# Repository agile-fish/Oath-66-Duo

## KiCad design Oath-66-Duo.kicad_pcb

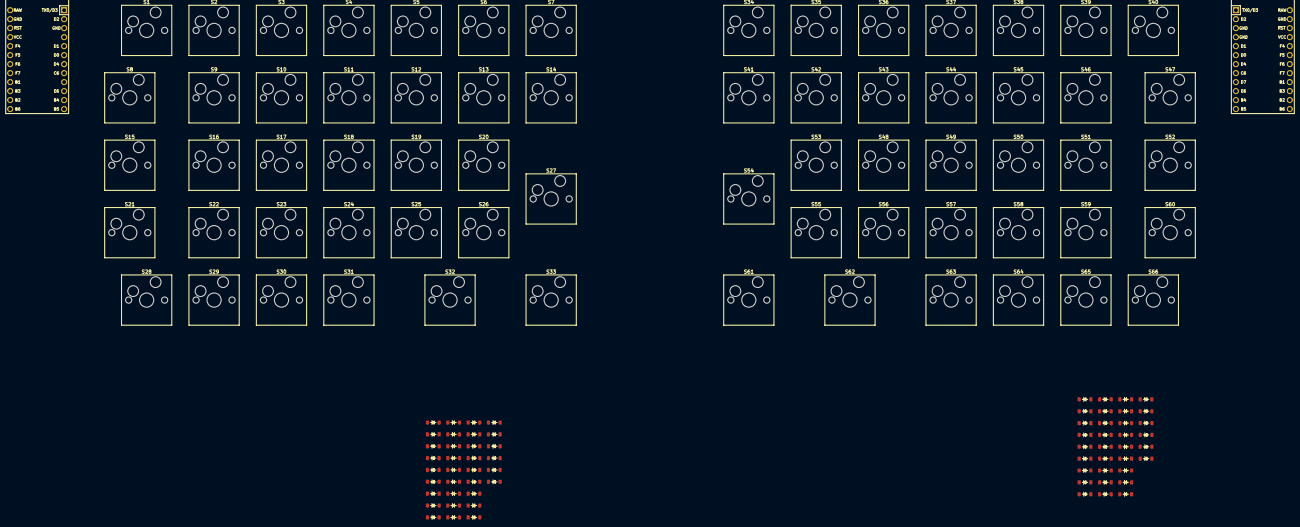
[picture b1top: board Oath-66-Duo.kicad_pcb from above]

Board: 2 copper layers, 134 parts (1 on the bottom side), 89 nets, no tracks yet.

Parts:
D1, D2, D3, D4, D5, D6, D7, D8, D9, D10, D11, D12, D13, D14, D15, D16, D17, D18, D19, D20, D21, D22, D23, D24, D25, D26, D27, D28, D29, D30, D31, D32, D33, D34, D35, D36, D37, D38, D39, D40, D41, D42, D43, D44, D45, D46, D47, D48, D49, D50, D51, D52, D53, D54, D55, D56, D57, D58, D59, D60, D61, D62, D63, D64, D65, D66: Diode; Diode_SOD-123
S1, S2, S3, S4, S5, S6, S7, S9, S10, S11, S12, S13, S14, S16, S17, S18, S19, S20, S22, S23, S24, S25, S26, S28, S29, S30, S31, S33, S34, S35, S36, S37, S38, S39, S40, S41, S42, S43, S44, S45, S46, S48, S49, S50, S51, S53, S55, S56, S57, S58, S59, S61, S63, S64, S65, S66: Keyswitch; Hotswap_MX_1.00u
S8, S15, S21, S47, S52, S60: Keyswitch; Hotswap_MX_1.50u
S27, S54: Keyswitch; Hotswap_MX_2.00u_90deg
S32, S62: Keyswitch; Hotswap_MX_2.00u
U1, U2: Arduino_Pro_Micro

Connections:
/Oath-66-Duo-Left/Col 0: S1.1, S8.1, S15.1, S21.1, S28.1, U1.8 (5/PC6)
/Oath-66-Duo-Left/Col 1: S2.1, S9.1, S16.1, S22.1, S29.1, U1.10 (7/PE6)
/Oath-66-Duo-Left/Col 2: S3.1, S10.1, S17.1, S23.1, S30.1, U1.11 (8/PB4)
/Oath-66-Duo-Left/Col 3: S4.1, S11.1, S18.1, S24.1, S31.1, U1.15 (14/PB3)
/Oath-66-Duo-Left/Col 4: S5.1, S12.1, S19.1, S25.1, S32.1, U1.13 (10/PB6)
/Oath-66-Duo-Left/Col 5: S6.1, S13.1, S20.1, S26.1, U1.5 (2/PD1)
/Oath-66-Duo-Left/Col 6: S7.1, S14.1, S27.1, S33.1, U1.6 (3/PD0)
/Oath-66-Duo-Left/Row 0: D1.1 (K), D2.1 (K), D3.1 (K), D4.1 (K), D5.1 (K), D6.1 (K), D7.1 (K), U1.7 (4/PD4)
/Oath-66-Duo-Left/Row 1: D8.1 (K), D9.1 (K), D10.1 (K), D11.1 (K), D12.1 (K), D13.1 (K), D14.1 (K), U1.9 (6/PD7)
/Oath-66-Duo-Left/Row 2: D15.1 (K), D16.1 (K), D17.1 (K), D18.1 (K), D19.1 (K), D20.1 (K), U1.12 (9/PB5)
/Oath-66-Duo-Left/Row 3: D21.1 (K), D22.1 (K), D23.1 (K), D24.1 (K), D25.1 (K), D26.1 (K), D27.1 (K), U1.16 (15/PB1)
/Oath-66-Duo-Left/Row 4: D28.1 (K), D29.1 (K), D30.1 (K), D31.1 (K), D32.1 (K), D33.1 (K), U1.14 (16/PB2)
/Oath-66-Duo-Right/Col 0: D48.1 (K), D49.1 (K), D50.1 (K), D51.1 (K), D52.1 (K), D53.1 (K), S34.1, S41.1, S54.1, S61.1, U2.8 (5/PC6), U2.12 (9/PB5)
/Oath-66-Duo-Right/Col 1: S35.1, S42.1, S48.1, S55.1, U2.10 (7/PE6)
/Oath-66-Duo-Right/Col 2: S36.1, S43.1, S49.1, S56.1, S62.1, U2.11 (8/PB4)
/Oath-66-Duo-Right/Col 3: S37.1, S44.1, S50.1, S57.1, S63.1, U2.15 (14/PB3)
/Oath-66-Duo-Right/Col 4: S38.1, S45.1, S51.1, S58.1, S64.1, U2.13 (10/PB6)
/Oath-66-Duo-Right/Col 5: S39.1, S46.1, S52.1, S59.1, S65.1, U2.5 (2/PD1)
/Oath-66-Duo-Right/Col 6: S40.1, S47.1, S53.1, S60.1, S66.1, U2.6 (3/PD0)
/Oath-66-Duo-Right/Row 0: D34.1 (K), D35.1 (K), D36.1 (K), D37.1 (K), D38.1 (K), D39.1 (K), D40.1 (K), U2.7 (4/PD4)
/Oath-66-Duo-Right/Row 1: D41.1 (K), D42.1 (K), D43.1 (K), D44.1 (K), D45.1 (K), D46.1 (K), D47.1 (K), U2.9 (6/PD7)
/Oath-66-Duo-Right/Row 3: D54.1 (K), D55.1 (K), D56.1 (K), D57.1 (K), D58.1 (K), D59.1 (K), D60.1 (K), U2.16 (15/PB1)
/Oath-66-Duo-Right/Row 4: D61.1 (K), D62.1 (K), D63.1 (K), D64.1 (K), D65.1 (K), D66.1 (K), U2.14 (16/PB2)
unnamed: D1.2 (A), S1.2
unnamed: D2.2 (A), S2.2
unnamed: D3.2 (A), S3.2
unnamed: D4.2 (A), S4.2
unnamed: D5.2 (A), S5.2
unnamed: D6.2 (A), S6.2
unnamed: D7.2 (A), S7.2
unnamed: D8.2 (A), S8.2
unnamed: D9.2 (A), S9.2
unnamed: D10.2 (A), S10.2
unnamed: D11.2 (A), S11.2
unnamed: D12.2 (A), S12.2
unnamed: D13.2 (A), S13.2
unnamed: D14.2 (A), S14.2
unnamed: D15.2 (A), S15.2
unnamed: D16.2 (A), S16.2
unnamed: D17.2 (A), S17.2
unnamed: D18.2 (A), S18.2
unnamed: D19.2 (A), S19.2
unnamed: D20.2 (A), S20.2
unnamed: D21.2 (A), S21.2
unnamed: D22.2 (A), S22.2
unnamed: D23.2 (A), S23.2
unnamed: D24.2 (A), S24.2
unnamed: D25.2 (A), S25.2
unnamed: D26.2 (A), S26.2
unnamed: D27.2 (A), S27.2
unnamed: D28.2 (A), S28.2
unnamed: D29.2 (A), S29.2
unnamed: D30.2 (A), S30.2
unnamed: D31.2 (A), S31.2
unnamed: D32.2 (A), S32.2
unnamed: D33.2 (A), S33.2
unnamed: D34.2 (A), S34.2
unnamed: D35.2 (A), S35.2
unnamed: D36.2 (A), S36.2
unnamed: D37.2 (A), S37.2
unnamed: D38.2 (A), S38.2
unnamed: D39.2 (A), S39.2
unnamed: D40.2 (A), S40.2
unnamed: D41.2 (A), S41.2
unnamed: D42.2 (A), S42.2
unnamed: D43.2 (A), S43.2
unnamed: D44.2 (A), S44.2
unnamed: D45.2 (A), S45.2
unnamed: D46.2 (A), S46.2
unnamed: D47.2 (A), S47.2
unnamed: D48.2 (A), S48.2
unnamed: D49.2 (A), S49.2
unnamed: D50.2 (A), S50.2
unnamed: D51.2 (A), S51.2
unnamed: D52.2 (A), S52.2
unnamed: D53.2 (A), S53.2
unnamed: D54.2 (A), S54.2
unnamed: D55.2 (A), S55.2
unnamed: D56.2 (A), S56.2
unnamed: D57.2 (A), S57.2
unnamed: D58.2 (A), S58.2
unnamed: D59.2 (A), S59.2
unnamed: D60.2 (A), S60.2
unnamed: D61.2 (A), S61.2
unnamed: D62.2 (A), S62.2
unnamed: D63.2 (A), S63.2
unnamed: D64.2 (A), S64.2
unnamed: D65.2 (A), S65.2
unnamed: D66.2 (A), S66.2

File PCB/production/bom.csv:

Designator,Footprint,Quantity,Value,LCSC Part #
"D1, D10, D11, D12, D13, D14, D15, D16, D17, D18, D19, D2, D20, D21, D22, D23, D24, D25, D26, D27, D28, D29, D3, D30, D31, D32, D33, D4, D5, D6, D7, D8, D9",Diode_SOD-123,33,Diode,
"S1, S10, S11, S12, S13, S14, S15, S16, S17, S18, S19, S2, S20, S21, S22, S23, S24, S25, S26, S28, S29, S3, S30, S31, S33, S4, S5, S6, S7, S8, S9",Hotswap_MX_1.00u,31,Keyswitch,
S27,Hotswap_MX_2.00u_90deg,1,Keyswitch,
S32,Hotswap_MX_2.00u,1,Keyswitch,
U1,Arduino_Pro_Micro,1,Arduino_Pro_Micro,

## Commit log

2025-06-24 Initialize project
2025-06-26 Schematic Updated
2025-06-26 PCB Updated
2025-06-26 Schematic and PVB updated
2025-07-11 Sub-Schematic Updated
2025-07-15 Reorganised the file directory
2025-07-15 Recovery
2025-07-28 Schematic and PCB Updated
2025-07-29 PCB Routing Finished
2025-07-30 Bug Fixed
2025-08-04 Prepared for production
2025-08-25 Battery Connector Updated
2025-09-04 Firmware Updated
